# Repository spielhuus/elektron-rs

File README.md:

# elektron

The elektron package is a continuous integration and simulation tool for electronics projects.

Features
* Create output files from the command line
* Run erc and drc checks
* Create bom as json and Excel files.
* Programmatically create schemas with python code.
* Run spice simulation
* Convert markdown notebook files

## Installation

The elekron package can be installed locally or by using a [docker](https://github.com/spielhuus/elektron-docker) image.

Install the [Kicad](http://kicad.org) packages:

ubuntu 

```
apt-get install kicad kicad-symbols kicad-packages3d python3 python3-pip python3-venv
```

arch linux

```
pacman -Sy kicad kicad-library kicad-library-3d python python-pip
```
Install elektron from [PyPI](https://pypi.org/project/elektron-rs/)

```
python -m venv --system-site-packages .venv
pip install elektron-rs
```

The `--system-site-packages` option is needed to make elektron find the pcbnew packages.

Install the [osifont](https://github.com/hikikomori82/osifont).

```
mkdir -p /usr/local/share/fonts/TT/
curl -L "https://github.com/hikikomori82/osifont/blob/master/osifont-lgpl3fe.ttf?raw=true" -o /usr/local/share/fonts/TT/osifont-lgpl3fe.ttf
```

## Install from source

Install the required packages, note that Kicad and osifont are needed:

ubuntu 
```
apt-get install build-essential git cargo pkg-config libcairo2-dev libpango1.0-dev libngspice0-dev libpoppler-glib-dev libssl-dev libclang-14-dev
alias python='python3'
```

arch linux

```
pacman -Sy base-devel git clang python rustup graphite cairo pango ngspice poppler-glib
rustup default stable
```

Get and compile the code:

```
git clone https://github.com/spielhuus/elektron-rs
cd elektron-rs
make all
```

The `make` command will create the executable `elektron` in `.venv/bin`.

## Example usage

```
source .venv/bin/activate
elektron plot --input your_schema.kicad_sch --output schema.svg

```

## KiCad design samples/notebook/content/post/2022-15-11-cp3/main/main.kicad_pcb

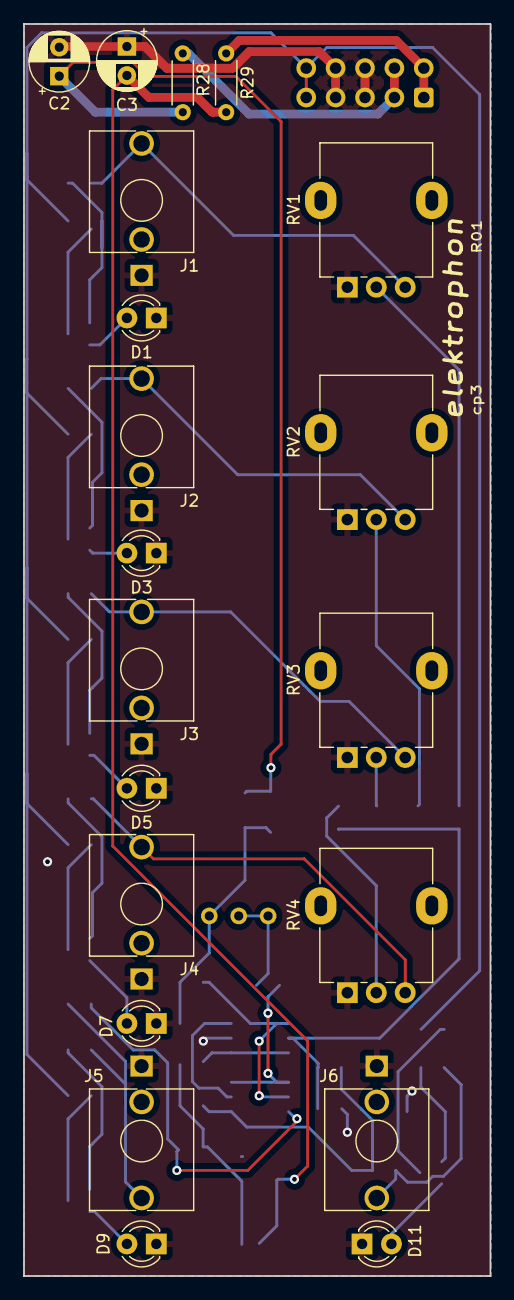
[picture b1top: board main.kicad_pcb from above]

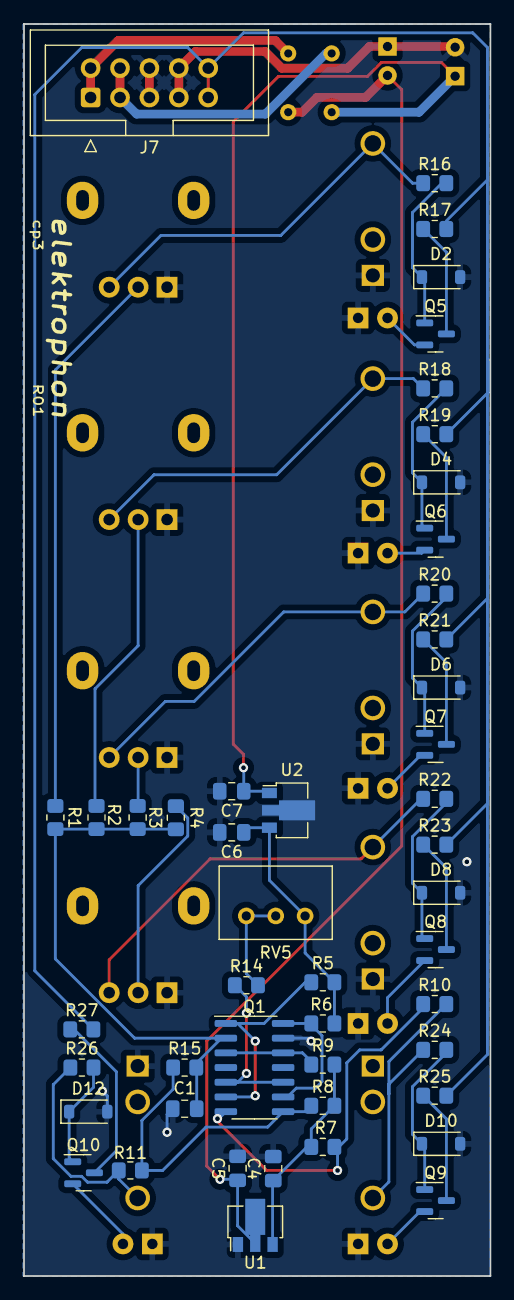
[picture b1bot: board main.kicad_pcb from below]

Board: 2 copper layers, 40.3 x 108.2 mm, 67 parts (47 on the bottom side), 44 nets.

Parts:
C1: 3.3n; C_0805_2012Metric_Pad1.18x1.45mm_HandSolder
C2, C3: 10u; CP_Radial_D5.0mm_P2.50mm
C4, C6: 0.33u; C_0805_2012Metric_Pad1.18x1.45mm_HandSolder
C5: 1.0u; C_0805_2012Metric_Pad1.18x1.45mm_HandSolder
C7: 0.01; C_0805_2012Metric_Pad1.18x1.45mm_HandSolder
D1, D3, D5, D7: LED (Green); LED_D3.0mm
D2, D4, D6, D8, D10, D12: 1N4148W; D_SOD-123
D9, D11: LED (Red); LED_D3.0mm
J1, J2, J3, J4, J5, J6: PJ398SM; Jack_3.5mm_WQP-PJ398SM_Vertical
J7: IDC_Header; IDC-Header_2x05_P2.54mm_Vertical
Q1: THAT340; SOIC-14_3.9x8.7mm_P1.27mm
Q5, Q6, Q7, Q8, Q9, Q10: MMBT3904; SOT-23
R1, R2, R3, R4: 22k; R_0805_2012Metric_Pad1.20x1.40mm_HandSolder
R5, R6: 15k; R_0805_2012Metric_Pad1.20x1.40mm_HandSolder
R7, R8: 560; R_0805_2012Metric_Pad1.20x1.40mm_HandSolder
R9: 6.8k; R_0805_2012Metric_Pad1.20x1.40mm_HandSolder
R10, R11: 100; R_0805_2012Metric_Pad1.20x1.40mm_HandSolder
R14: 200; R_0805_2012Metric_Pad1.20x1.40mm_HandSolder
R15: 47k; R_0805_2012Metric_Pad1.20x1.40mm_HandSolder
R16, R18, R20, R22, R24, R26: 100k; R_0805_2012Metric_Pad1.20x1.40mm_HandSolder
R17, R19, R21, R23, R25, R27: 5.1k; R_0805_2012Metric_Pad1.20x1.40mm_HandSolder
R28, R29: 10; R_Axial_DIN0204_L3.6mm_D1.6mm_P5.08mm_Horizontal
RV1, RV2, RV3, RV4: 50k (A); Potentiometer_Alpha_RD901F-40-00D_Single_Vertical
RV5: 100; Potentiometer_Bourns_3299W_Vertical
U1: NJM79L06; SOT-89-3
U2: uA7812; SOT-89-3

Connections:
+5V: J7.9, J7.10, R17.2, R19.2, R21.2, R23.2, R25.2, R27.2
+12V: C6.1, R5.2, R6.1, RV5.3, U2.3 (OUT)
+15V: C2.1, C7.1, R28.2, U2.1 (IN)
-6V: C4.1, R7.2, R8.2, R9.2, U1.3 (VO)
-15V: C3.2, C5.1, R29.1, U1.2 (VI)
/IN_1: R1.1, RV1.2
/IN_2: R2.2, RV2.2
/IN_3: R3.2, RV3.2
/IN_4: R4.2, RV4.2
/IN_a: J1.T, R16.1, RV1.3
/IN_b: J2.T, R18.1, RV2.3
/IN_c: J3.T, R20.1, RV3.3
/IN_d: J4.T, R22.1, RV4.3
/OUT_A: J5.T, R10.2, R24.1
/OUT_B: J6.T, R11.2, R26.1
/VN: J7.1, J7.2, R29.2
/VP: J7.3, J7.4, R28.1
GND: C1.2, C2.2, C3.1, C4.2, C5.2, C6.2, C7.2, D1.1 (K), D2.2 (A), D3.1 (K), D4.2 (A), D5.1 (K), D6.2 (A), D7.1 (K), D8.2 (A), D9.1 (K), D10.2 (A), D11.1 (K), D12.2 (A), J1.S, J2.S, J3.S, J4.S, J5.S, J6.S, J7.5, J7.6, J7.7, J7.8, Q1.13 (B), RV1.1, RV2.1, RV3.1, RV4.1, U1.1 (GND), U2.2 (GND)
unnamed: D1.2 (A), Q5.2 (E)
unnamed: D2.1 (K), Q5.1 (B), R16.2
unnamed: D3.2 (A), Q6.2 (E)
unnamed: D4.1 (K), Q6.1 (B), R18.2
unnamed: D5.2 (A), Q7.2 (E)
unnamed: D6.1 (K), Q7.1 (B), R20.2
unnamed: D7.2 (A), Q8.2 (E)
unnamed: D8.1 (K), Q8.1 (B), R22.2
unnamed: D9.2 (A), Q9.2 (E)
unnamed: D10.1 (K), Q9.1 (B), R24.2
unnamed: D11.2 (A), Q10.2 (E)
unnamed: D12.1 (K), Q10.1 (B), R26.2
unnamed: C1.1, Q1.2 (B), R1.2, R2.1, R3.1, R4.1, R15.2
unnamed: Q1.1 (C), Q1.6 (B), R5.1
unnamed: Q1.3 (E), Q1.12 (E), R9.1
unnamed: Q1.9 (B), Q1.14 (C), R6.2
unnamed: Q1.5 (C), Q1.10, R14.1
unnamed: Q1.7 (E), R7.1, R10.1
unnamed: Q1.8 (E), R8.1, R11.1, R15.1
unnamed: Q5.3 (C), R17.1
unnamed: Q6.3 (C), R19.1
unnamed: Q7.3 (C), R21.1
unnamed: Q8.3 (C), R23.1
unnamed: Q9.3 (C), R25.1
unnamed: Q10.3 (C), R27.1
unnamed: R14.2, RV5.1, RV5.2

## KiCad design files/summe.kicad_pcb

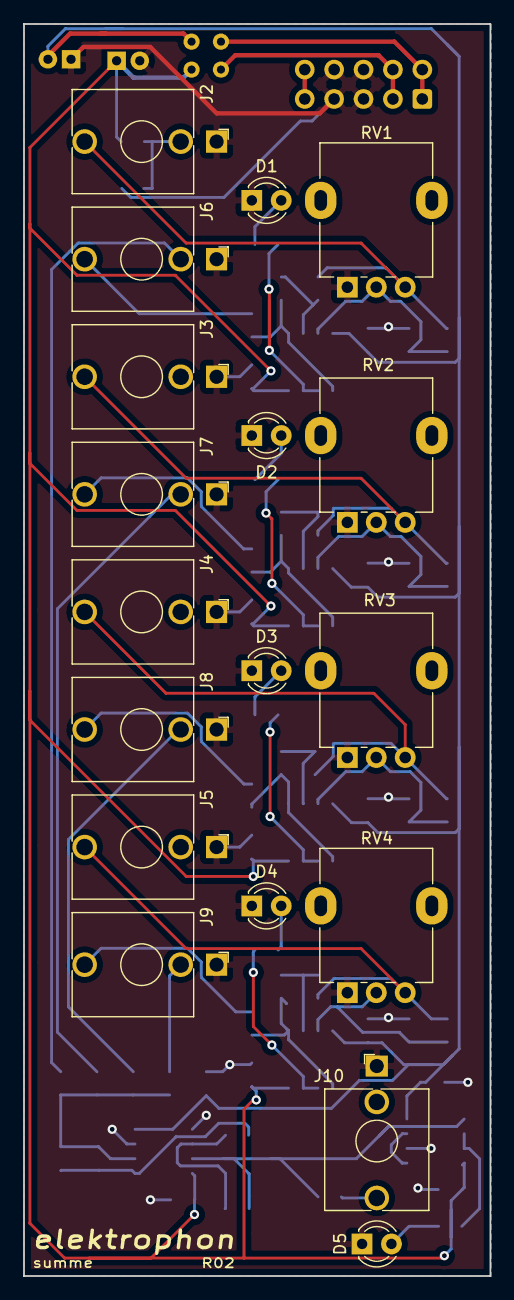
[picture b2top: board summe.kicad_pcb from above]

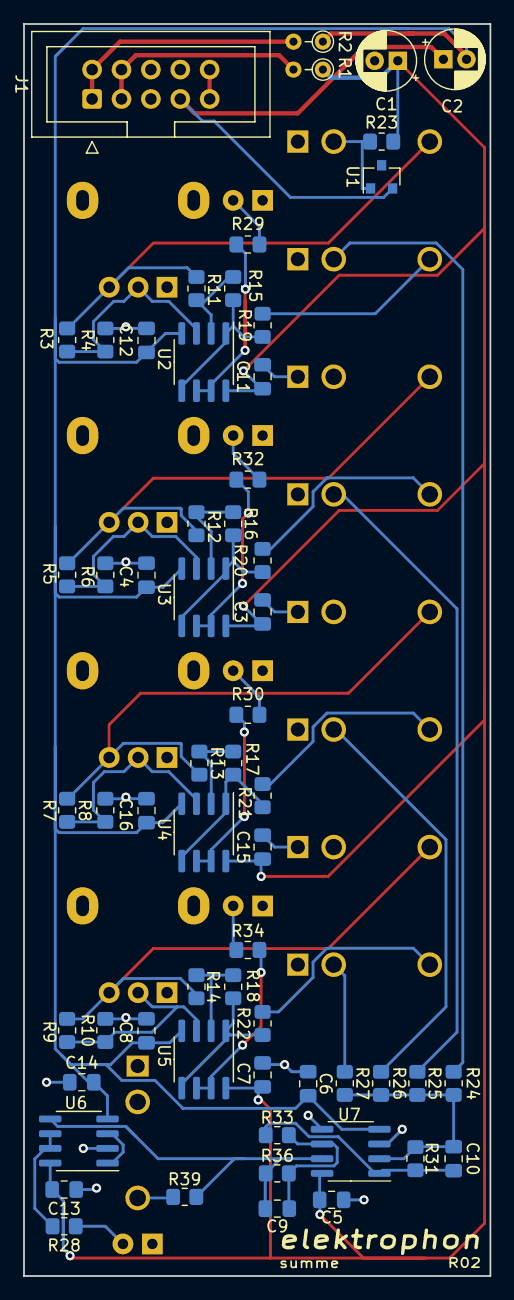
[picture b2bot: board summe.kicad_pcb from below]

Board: 2 copper layers, 40.3 x 108.2 mm, 78 parts (60 on the bottom side), 47 nets.

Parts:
C1, C2: 22u; CP_Radial_D5.0mm_P2.00mm
C3, C4, C5, C6, C7, C8, C11, C12, C13, C14, C15, C16: 0.1u; C_0805_2012Metric_Pad1.18x1.45mm_HandSolder
C9, C10: 100p; C_0805_2012Metric_Pad1.18x1.45mm_HandSolder
D1, D2, D3, D4: LED (Green/Yellow); LED_D3.0mm
D5: LED (Red/Yellow); LED_D3.0mm
J1: IDC Header; IDC-Header_2x05_P2.54mm_Vertical
J2, J3, J4, J5: IN; Jack_3.5mm_WQP-PJ398SM_Vertical
J6, J7, J8, J9, J10: OUT; Jack_3.5mm_WQP-PJ398SM_Vertical
R1, R2: 10; R_Axial_DIN0204_L3.6mm_D1.6mm_P2.54mm_Vertical
R3, R4, R5, R6, R7, R8, R9, R10: 47k; R_0805_2012Metric_Pad1.20x1.40mm_HandSolder
R11, R12, R13, R14, R15, R16, R17, R18, R24, R25, R26, R27, R31, R33, R36: 100k; R_0805_2012Metric_Pad1.20x1.40mm_HandSolder
R19, R20, R21, R22, R39: 1k; R_0805_2012Metric_Pad1.20x1.40mm_HandSolder
R23: 8.2k; R_0805_2012Metric_Pad1.20x1.40mm_HandSolder
R28, R29, R30, R32, R34: 500; R_0805_2012Metric_Pad1.20x1.40mm_HandSolder
RV1, RV2, RV3, RV4: 100k; Potentiometer_Alpha_RD901F-40-00D_Single_Vertical
U1: LM4040BIM3-5.0; SOT-23
U2, U3, U4, U5, U6, U7: TL072; SOIC-8_3.9x4.9mm_P1.27mm

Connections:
+5V: J1.9, J1.10
+15V: C1.1, C3.1, C5.1, C7.1, C11.1, C13.1, C15.1, R1.1, R23.2, U2.8, U3.8, U4.8, U5.8, U6.8, U7.8
-15V: C2.2, C4.2, C6.2, C8.2, C12.2, C14.2, C16.2, R2.1, U2.4, U3.4, U4.4, U5.4, U6.4, U7.4
/IN_1: R15.1, R19.1, U2.1, U2.5
/IN_2: R16.1, R20.1, U3.1, U3.5
/IN_3: R17.1, R21.1, U4.1, U4.5
/IN_4: R18.1, R22.1, U5.1, U5.5
/MIX_1: J6.TN, R24.1
/MIX_2: J7.TN, R25.1
/MIX_3: J8.TN, R26.1
/MIX_4: J9.TN, R27.1
/OUT: C9.1, R36.2, R39.1, U6.5, U7.7
/REF: J2.TN, R23.1, U1.1
GND: C1.2, C2.1, C3.2, C4.1, C5.2, C6.1, C7.2, C8.1, C11.2, C12.1, C13.2, C14.1, C15.2, C16.1, D1.1, D2.1, D3.1, D4.1, D5.1, J1.5, J1.6, J1.7, J1.8, J2.S, J3.S, J4.S, J5.S, J6.S, J7.S, J8.S, J9.S, J10.S, R4.2, R6.2, R8.2, R10.2, RV1.1, RV2.1, RV3.1, RV4.1, U1.2, U6.2, U7.3, U7.5
unnamed: C9.2, R33.2, R36.1, U7.6
unnamed: C10.1, R31.2, R33.1, U7.1
unnamed: C10.2, R24.2, R25.2, R26.2, R27.2, R31.1, U7.2
unnamed: D1.2, R29.1
unnamed: D2.2, R32.1
unnamed: D3.2, R30.1
unnamed: D4.2, R34.1
unnamed: D5.2, R28.1
unnamed: J2.T, R3.1, R11.2, RV1.3
unnamed: J3.T, R5.1, R12.2, RV2.3
unnamed: J4.T, R7.1, R13.2, RV3.3
unnamed: J5.T, R9.1, R14.2, RV4.3
unnamed: J6.T, R19.2
unnamed: J7.T, R20.2
unnamed: J8.T, R21.2
unnamed: J9.T, R22.2
unnamed: J10.T, R39.2
unnamed: R3.2, R4.1, RV1.2, U2.3
unnamed: R5.2, R6.1, RV2.2, U3.3
unnamed: R7.2, R8.1, RV3.2, U4.3
unnamed: R9.2, R10.1, RV4.2, U5.3
unnamed: R11.1, R15.2, U2.2
unnamed: R12.1, R16.2, U3.2
unnamed: R13.1, R17.2, U4.2
unnamed: R14.1, R18.2, U5.2
unnamed: R28.2, U6.6, U6.7
unnamed: R29.2, U2.6, U2.7
unnamed: R30.2, U4.6, U4.7
unnamed: R32.2, U3.6, U3.7
unnamed: R34.2, U5.6, U5.7
unnamed: U6.1, U6.3
VN: J1.1, J1.2, R2.2
VP: J1.3, J1.4, R1.2

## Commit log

2022-07-05 initial import
2022-07-18 refactoring
2022-07-18 update python version
2022-07-19 fix quoted string in parser
2022-07-19 set library name and wire pts
2022-07-22 update plot
2022-07-24 update some things
2022-07-25 add ngspice sim.h
2022-07-25 add plot to draw
2022-07-25 plot to stdout
2022-07-25 return plot as string
2022-07-25 add ipython dependency
2022-07-25 return spice values as Map
2022-07-26 scale plot
2022-07-26 update draw
2022-07-27 display
2022-07-29 add timing parameters to tran
2022-07-30 add subcicuit
2022-07-30 set circuit value
2022-08-01 change to setuptools-rust build tool
2022-08-01 output search results
2022-08-01 dump to file
2022-08-01 handle symbols without library entry
2022-08-01 cleanup
2022-09-04 refactor draw
2022-09-04 cleanup spice and add ELEKTRON_DEBUG
2022-09-04 remove print statements
2022-09-04 do some stuff
2022-09-05 implement all schema elements
2022-09-11 add pcb parser and plotter
2022-09-18 refactor and work on netlist
2022-09-19 update netlist
2022-10-02 update files
2022-10-02 rename python package
2023-06-03 new version
2023-06-03 update buildfile
2023-06-03 add openssl to build process
2023-06-03 add libpoppler to build process
2023-06-03 update all versions
2023-06-03 generate css files
2023-06-03 create sdisk package
2023-06-03 create disk package
2023-06-03 add graphite
2023-06-03 skip tests
2023-06-04 update python versions
2023-06-04 update release version
2023-06-04 add css files
2023-06-04 do not remove the css files
2023-06-05 add count to missing bom items
2023-06-25 update dependencies
2023-10-17 update to new structure
2023-10-17 add files to sdist
2023-10-17 update pipy project name
2023-10-17 change project name
2023-10-19 change to maturin build system
2023-10-20 remove auto-initialize
2023-10-21 try release
2023-10-26 update release
2023-10-27 cleanup clippy messages
2023-10-29 cleanup build configuration
2023-12-23 code cleanup
2024-01-03 correct erc for unconnected pins
2024-01-03 add list to main function for nvim plugin
2024-01-03 update version
2024-02-25 add binary harfbuzz
2024-02-26 fix typos in build files
2024-03-21 update manylinux
2024-03-22 refactor and parse notebooks without pest
2024-03-23 update gihub actions
2024-03-23 refactor notebook
2024-03-23 add kicad symbols
2024-03-23 fix clippy warnings
2024-03-23 ngspice dependency
2024-03-23 update github action
2024-03-24 disable tests
2024-03-24 add font
2024-03-24 add new documentation action.
2024-03-24 add doc makefile
2024-03-24 add description in README.md
2024-03-24 update doc description
2024-03-24 add readthedocs config file.
2024-03-24 add read the docs badge.
2024-03-24 remove doc action
2024-03-24 update documentation
2024-04-06 refactor the schema plotter
2024-04-06 add benchmark
2024-04-06 add schema for benchmark
2024-04-07 update pyo3 and some code cleanup
2024-04-08 add page size to header
2024-04-09 work on schema plotter and fix logging for drc
2024-04-12 implement schema plotter and use kicad-cli for drc tests
2024-04-12 add a schema with all elements
2024-04-17 update draw arc in plotter and work on docs
2024-04-18 FIX: handle text bounds with alignment
2024-04-18 work on documentation
2024-04-22 improve notebook error handling and logging
2024-04-22 supress clippy warnings
2024-04-23 move main function to rust lib and use clap
2024-04-23 update to the failed github build
2024-04-24 Update test.yml
    update package list before installing dependencies.
2024-04-27 FIX: Property placement of elements with single pin, ie Gnd
2024-04-27 cleanup error handling
2024-04-27 update error handling and handle pcb
2024-04-27 add temporary files
2024-04-27 start with pcbplotter
2024-04-27 FIX: property placement with no angle but mirror 'x'
2024-05-01 FEATURE: add pcb plotter
2024-05-01 FIX: handle some pcb plotter problems
2024-05-02 FIX: css class is svg plotter
2024-05-02 work on pcb plotter
2024-05-02 update gitignore
2024-05-06 work on pcb plot
2024-05-10 do a lot with the plotter
2024-05-15 before branch
2024-05-22 thunk about 2d graphics
2024-05-25 some updates
2024-09-03 Bump actions/download-artifact
    Bumps the github_actions group with 1 update in the /.github/workflows directory: [actions/download-artifact](https://github.com/actions/download-artifact).
    Updates `actions/download-artifact` from 3 to 4.1.7
    - [Release notes](https://github.com/actions/download-artifact/releases)
    - [Commits](https://github.com/actions/download-artifact/compare/v3...v4.1.7)
    ---
    updated-dependencies:

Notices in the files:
files/summe.kicad_pcb:
License CC BY 4.0 - Attribution 4.0 International
